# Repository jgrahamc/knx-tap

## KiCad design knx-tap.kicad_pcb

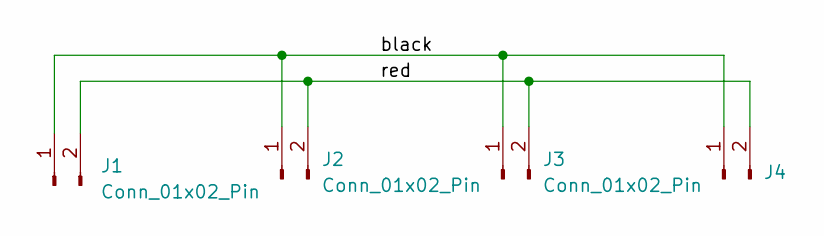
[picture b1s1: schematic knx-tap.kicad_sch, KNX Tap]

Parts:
J1, J2, J3, J4: Conn_01x02_Pin; Wago-243-211

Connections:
/black: J1.1, J2.1, J3.1, J4.1
/red: J1.2, J2.2, J3.2, J4.2

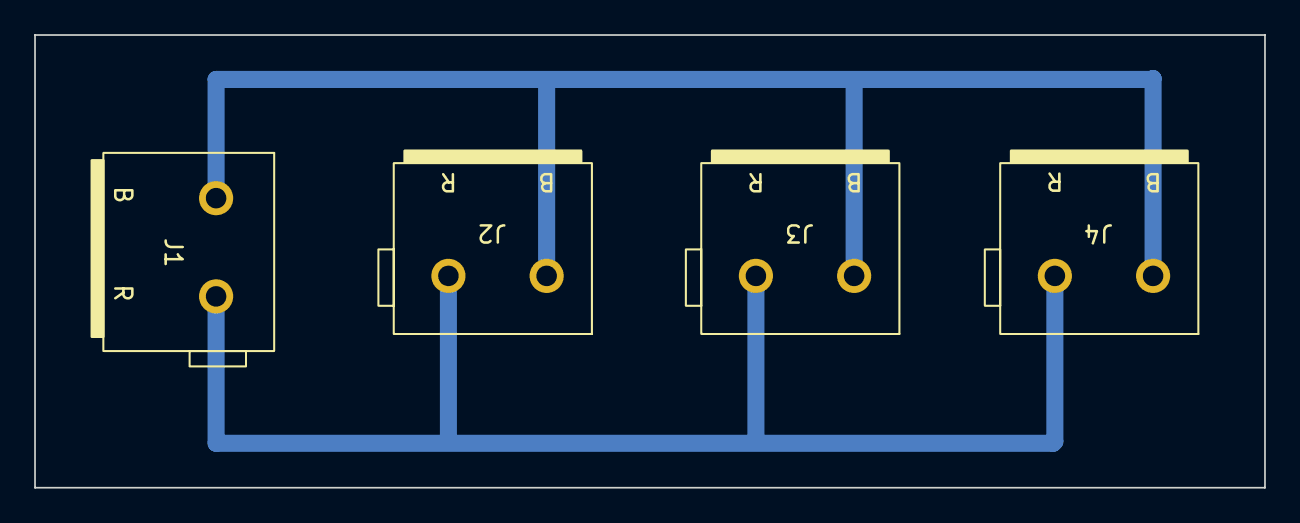
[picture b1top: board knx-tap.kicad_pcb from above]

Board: 2 copper layers, 72.0 x 26.5 mm, 4 parts (0 on the bottom side), 2 nets.

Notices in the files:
parts and their libraries:
STEP files are licensed under CC BY-ND 4.0 by PartsCommunity / PARTsolutions / CADENAS
